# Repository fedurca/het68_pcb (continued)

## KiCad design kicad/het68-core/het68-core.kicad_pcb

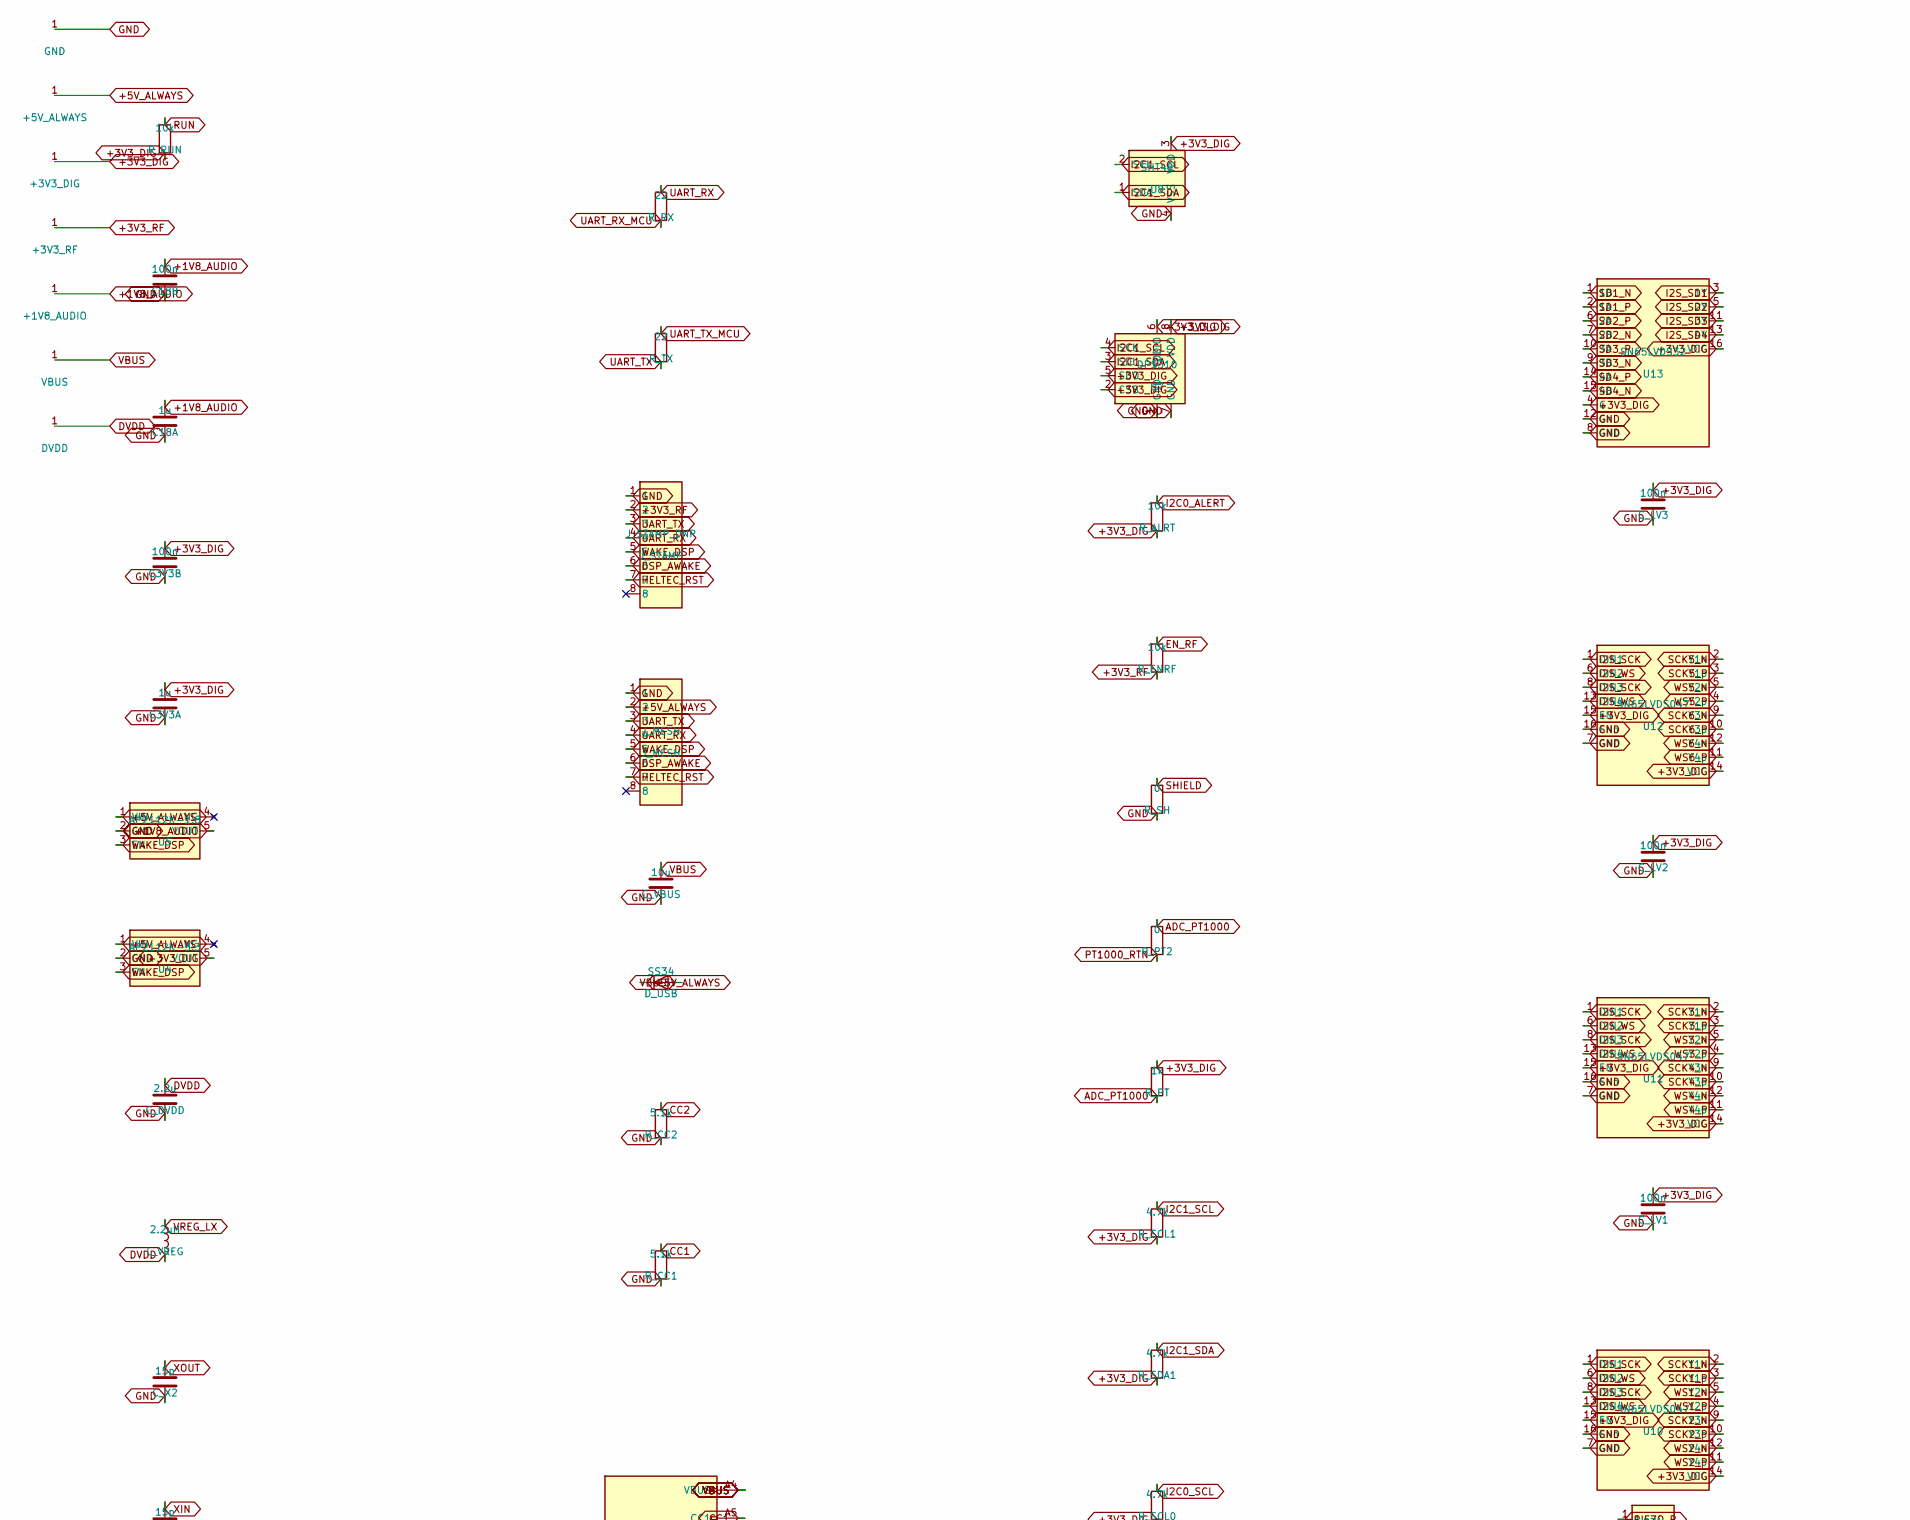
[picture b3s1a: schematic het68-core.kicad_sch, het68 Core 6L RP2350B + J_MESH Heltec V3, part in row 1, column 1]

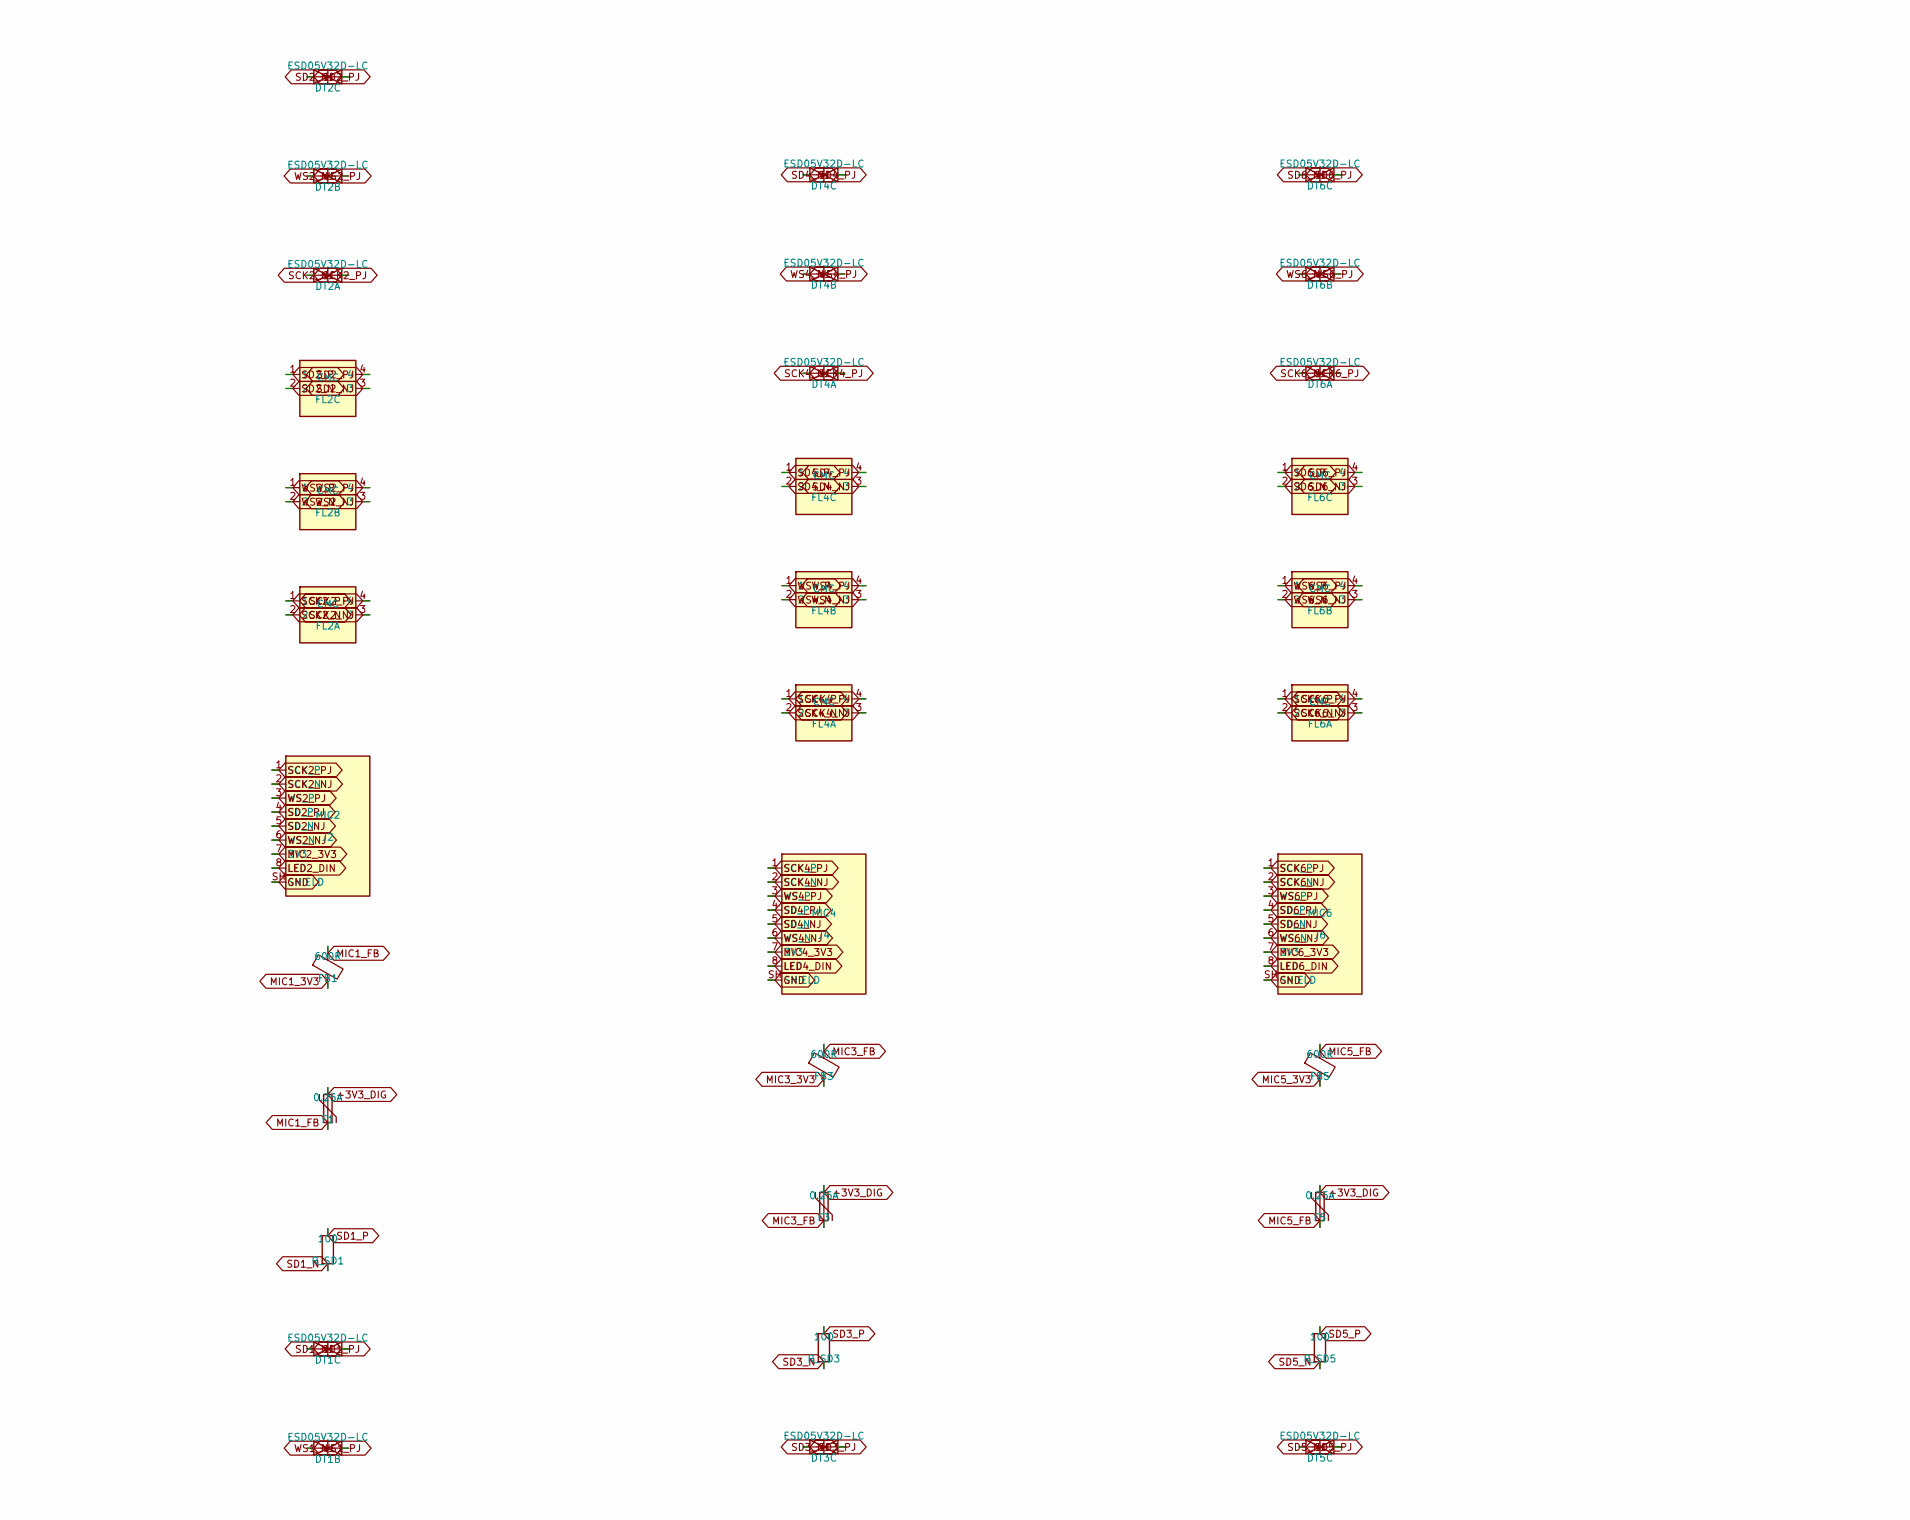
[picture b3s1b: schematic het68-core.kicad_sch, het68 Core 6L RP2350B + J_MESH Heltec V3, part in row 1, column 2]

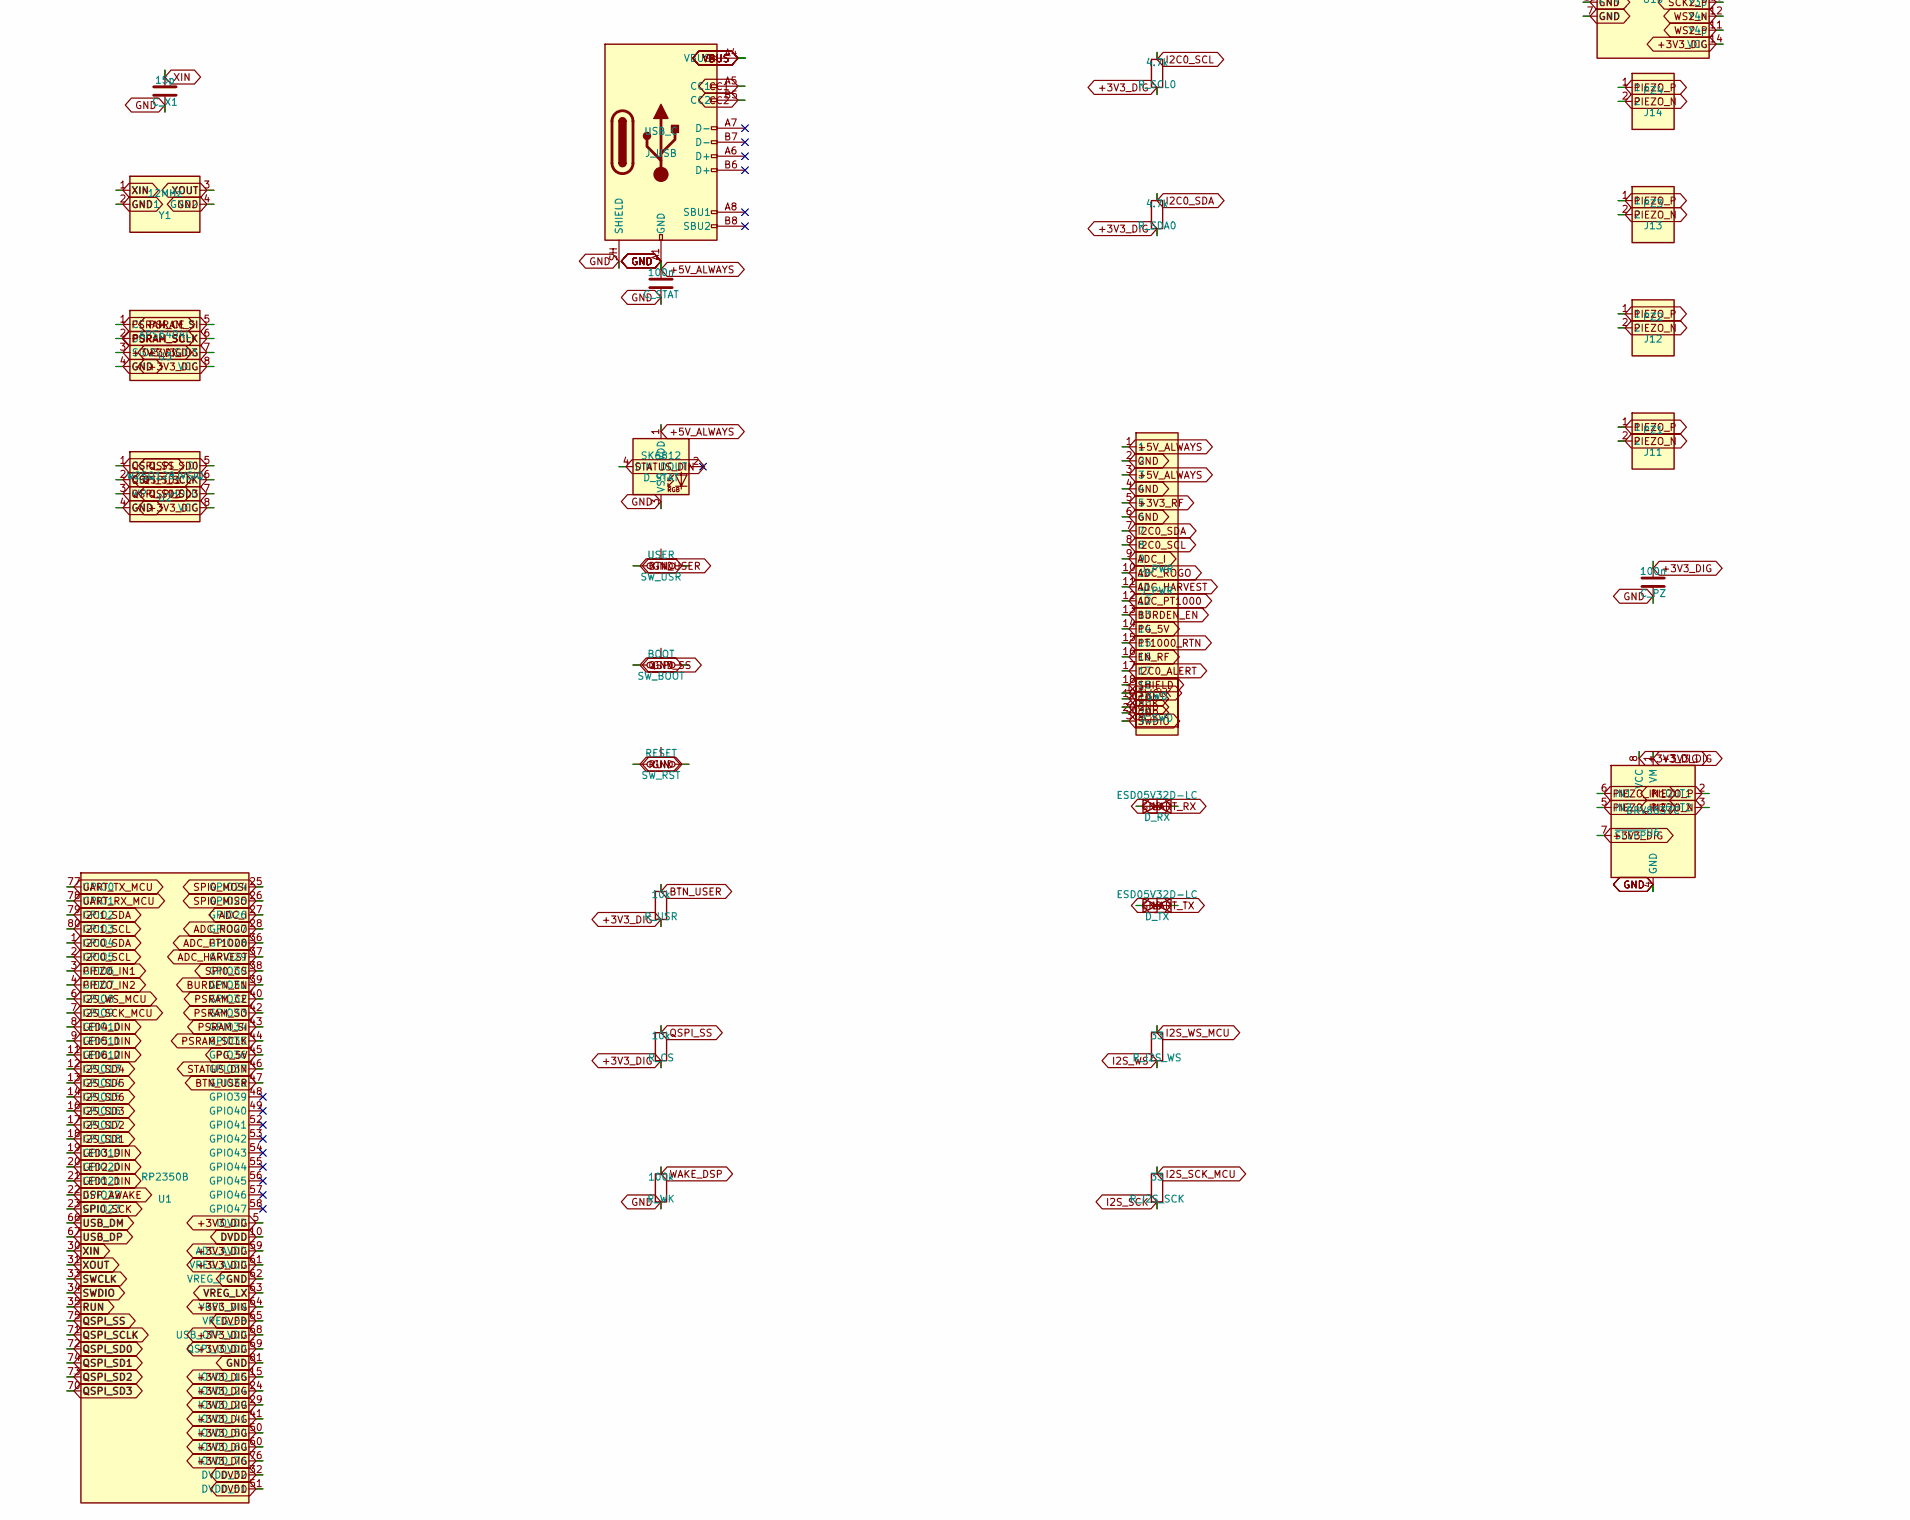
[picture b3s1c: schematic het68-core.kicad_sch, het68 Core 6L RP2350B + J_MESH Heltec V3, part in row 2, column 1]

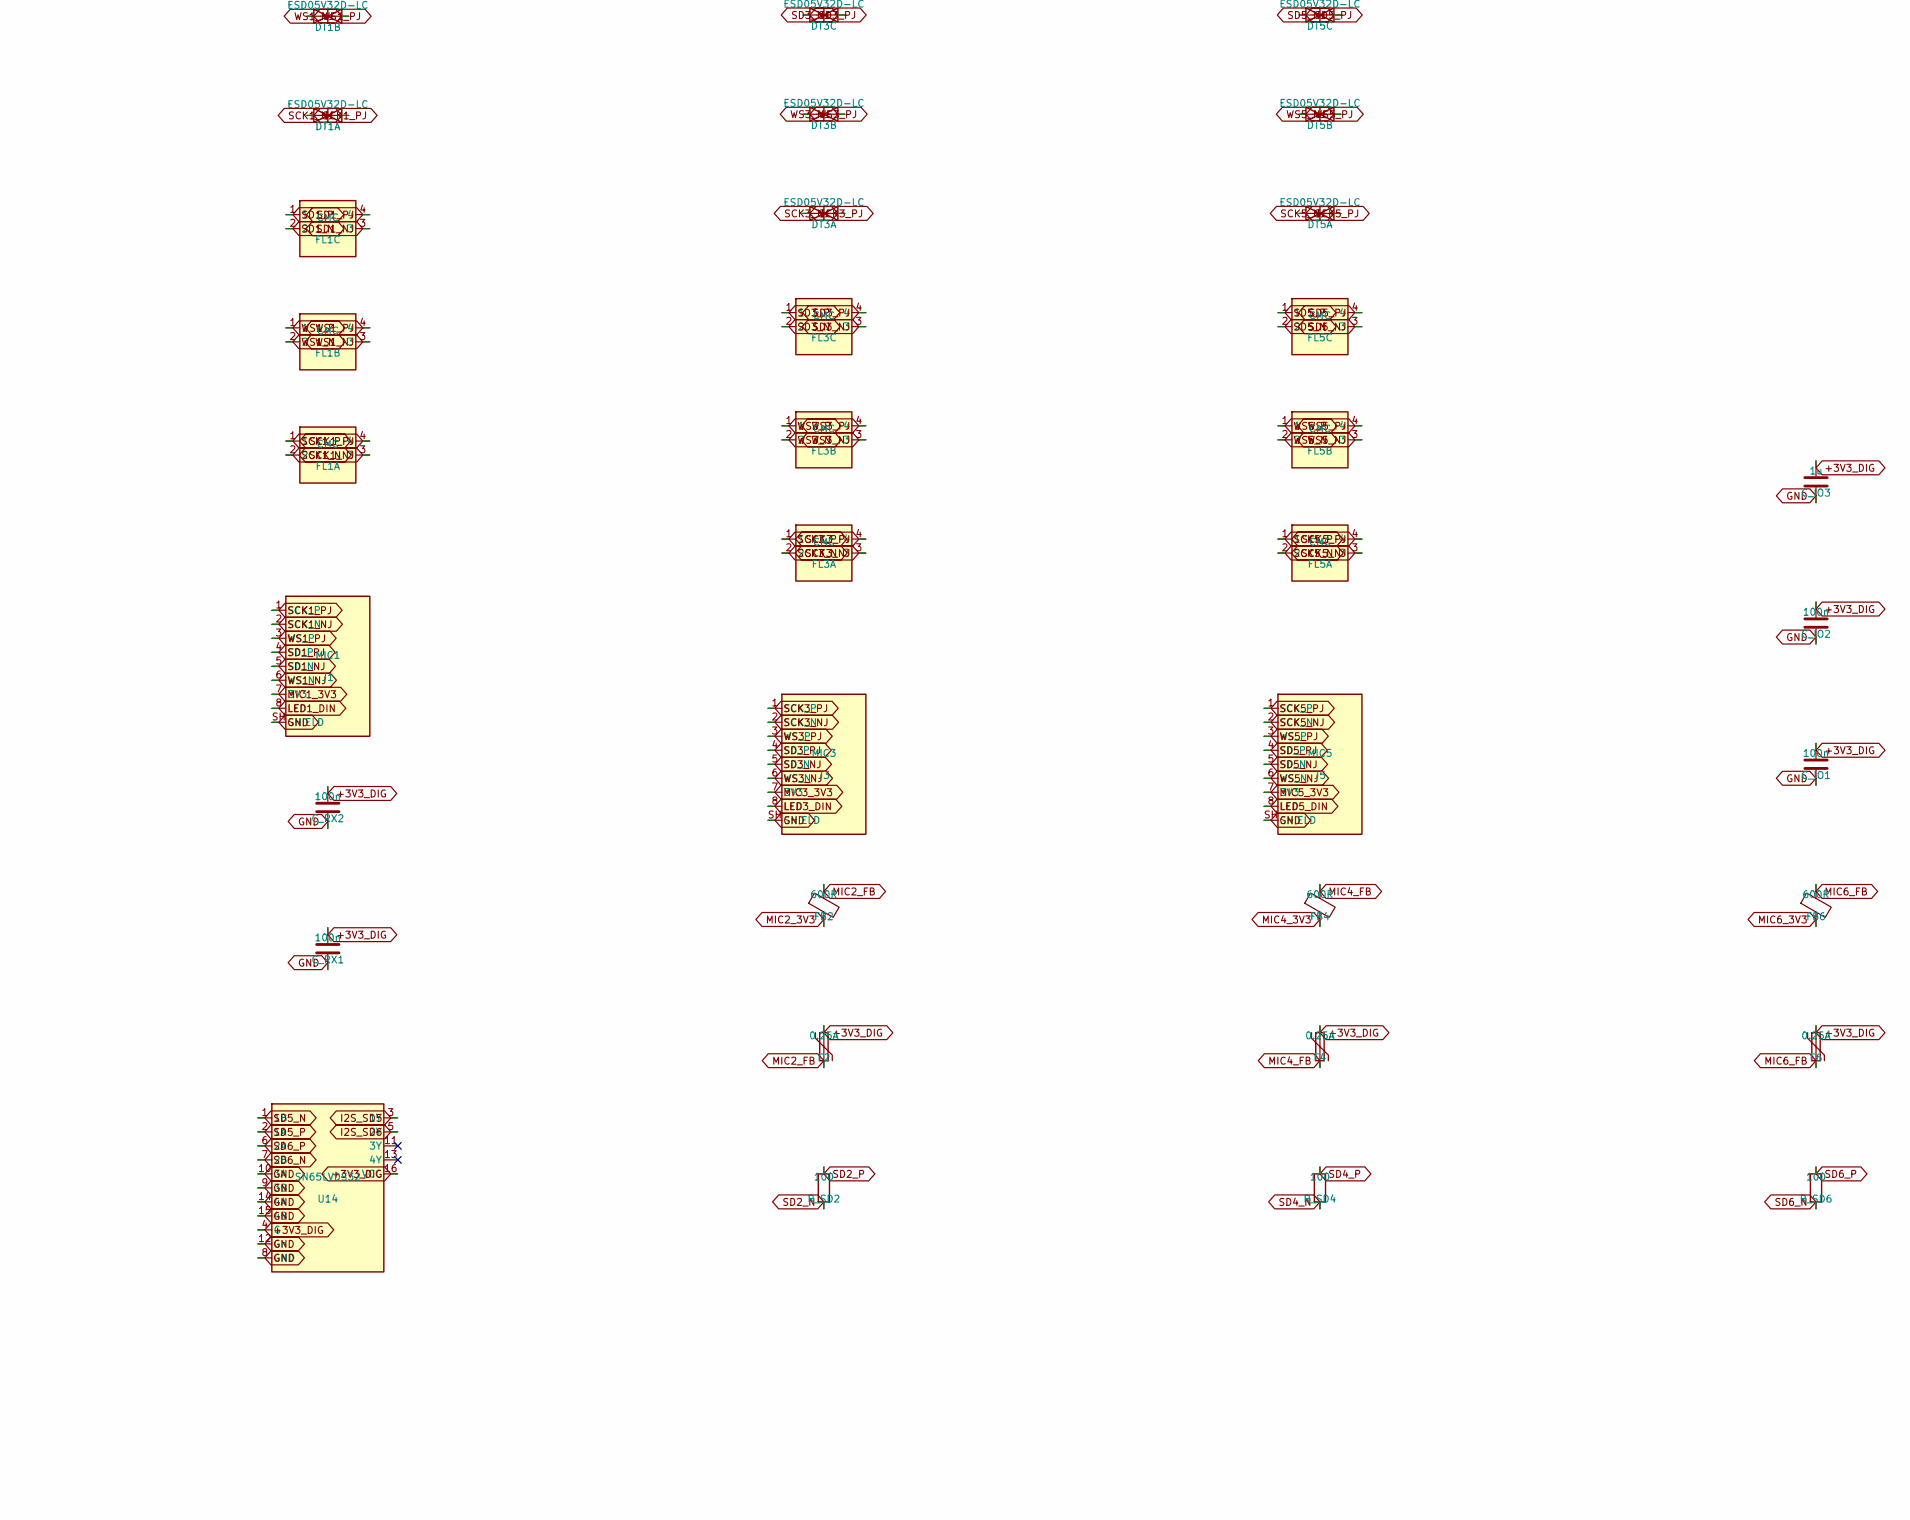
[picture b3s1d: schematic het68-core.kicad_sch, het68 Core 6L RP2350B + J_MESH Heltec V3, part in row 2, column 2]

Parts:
C3V3A, C18A: 1u; C_0603_1608Metric; MPN CL10A105KA8NNNC
C3V3B, C18B: 100n; C_0603_1608Metric; MPN CL10B104KB8NNNC
C_DVDD: 2.2u; C_0805_2012Metric; MPN CL21A225KOFNNNE
C_IO1, C_IO2: 100n; C_0603_1608Metric; MPN CL10B104KB8NNNC
C_IO3: 1u; C_0603_1608Metric; MPN CL10A105KA8NNNC
C_LV1, C_LV2, C_LV3: 100n; C_0603_1608Metric; MPN CL10B104KB8NNNC
C_PZ: 100n; C_0603_1608Metric; MPN CL10B104KB8NNNC
C_RX1, C_RX2: 100n; C_0603_1608Metric; MPN CL10B104KB8NNNC
C_STAT: 100n; C_0603_1608Metric; MPN CL10B104KB8NNNC
C_VBUS: 10u; C_0805_2012Metric; MPN CL21A106KOQNNNE
C_X1, C_X2: 15p; C_0603_1608Metric; MPN CL10C150JB8NNNC
DT1A, DT1B, DT1C, DT2A, DT2B, DT2C, DT3A, DT3B, DT3C, DT4A, DT4B, DT4C, DT5A, DT5B, DT5C, DT6A, DT6B, DT6C: ESD05V32D-LC; D_SOD-323; MPN ESD05V32D-LC
D_RX: ESD05V32D-LC; D_SOD-323; MPN ESD05V32D-LC
D_STAT: SK6812; LED_WS2812B_PLCC4_5.0x5.0mm_P3.2mm; MPN SK6812
D_TX: ESD05V32D-LC; D_SOD-323; MPN ESD05V32D-LC
D_USB: SS34; D_SMC; MPN SS34
F1, F2, F3, F4, F5, F6: 0.25A; Fuse_0603_1608Metric; MPN 0603L025/6V
FB1, FB2, FB3, FB4, FB5, FB6: 600R; L_0603_1608Metric; MPN BLM18AG601SN1D
FL1A, FL1B, FL1C, FL2A, FL2B, FL2C, FL3A, FL3B, FL3C, FL4A, FL4B, FL4C, FL5A, FL5B, FL5C, FL6A, FL6B, FL6C: CMC; L_CommonModeChoke_Coilank_ACM2012; MPN ACM2012-900-2P-T001
J1: MIC1; RJ45_Vertical_het68; MPN RJ45-8P8C-VERT
J2: MIC2; RJ45_Vertical_het68; MPN RJ45-8P8C-VERT
J3: MIC3; RJ45_Vertical_het68; MPN RJ45-8P8C-VERT
J4: MIC4; RJ45_Vertical_het68; MPN RJ45-8P8C-VERT
J5: MIC5; RJ45_Vertical_het68; MPN RJ45-8P8C-VERT
J6: MIC6; RJ45_Vertical_het68; MPN RJ45-8P8C-VERT
J11: PZ1; PinHeader_1x02_P2.54mm_Vertical; MPN PS1240
J12: PZ2; PinHeader_1x02_P2.54mm_Vertical; MPN PS1240
J13: PZ3; PinHeader_1x02_P2.54mm_Vertical; MPN PS1240
J14: PZ4; PinHeader_1x02_P2.54mm_Vertical; MPN PS1240
J_MESH: J_MESH; PinHeader_1x08_P2.54mm_Vertical; MPN PinHeader 1x8 Heltec V3
J_PWR: J_PWR; PinHeader_2x10_P2.54mm_Vertical; MPN interconnect 2x10
J_STAMP: J_STAMP_DNP; PinHeader_1x08_P2.54mm_Vertical; MPN DNP stamp RAK class
J_SWD: SWD; PinHeader_1x03_P2.54mm_Vertical; MPN SWD
J_USB: USB_C; USB_C_Receptacle_HRO_TYPE-C-31-M-12; MPN TYPE-C-31-M-12
L_VREG: 2.2uH; L_0805_2012Metric; MPN DFE201210U-2R2M=P2
R_ALRT: 10k; R_0603_1608Metric; MPN RC0603FR-0710KL
R_CC1, R_CC2: 5.1k; R_0603_1608Metric; MPN RC0603FR-075K1L
R_CS: 10k; R_0603_1608Metric; MPN RC0603FR-0710KL
R_ENRF: 10k; R_0603_1608Metric; MPN RC0603FR-0710KL
R_I2S_SCK, R_I2S_WS: 33; R_0603_1608Metric; MPN RC0603FR-0733RL
R_PT: 1k; R_0603_1608Metric; MPN RC0603FR-071KL
R_PT2: 0; R_0603_1608Metric; MPN RC0603FR-070RL
R_RUN: 10k; R_0603_1608Metric; MPN RC0603FR-0710KL
R_RX: 22; R_0603_1608Metric; MPN RC0603FR-0722RL
R_SCL0, R_SCL1: 4.7k; R_0603_1608Metric; MPN RC0603FR-074K7L
R_SD1, R_SD2, R_SD3, R_SD4, R_SD5, R_SD6: 100; R_0603_1608Metric; MPN RC0603FR-07100RL
R_SDA0, R_SDA1: 4.7k; R_0603_1608Metric; MPN RC0603FR-074K7L
R_SH: 0; R_0603_1608Metric; MPN RC0603FR-070RL
R_TX: 22; R_0603_1608Metric; MPN RC0603FR-0722RL
R_USR: 10k; R_0603_1608Metric; MPN RC0603FR-0710KL
R_WK: 100k; R_0603_1608Metric; MPN RC0603FR-07100KL
SW_BOOT: BOOT; SW_SPST_PTS645Sx43SMTR92; MPN PTS645SM43SMTR92LFS
SW_RST: RESET; SW_SPST_PTS645Sx43SMTR92; MPN PTS645SM43SMTR92LFS
SW_USR: USER; SW_SPST_PTS645Sx43SMTR92; MPN PTS645SM43SMTR92LFS
U1: RP2350B; QFN-80-1EP_10x10mm_P0.4mm_EP3.4x3.4mm_ThermalVias; MPN RP2350B
U2: W25Q128JVSIQ; SOIC-8_3.9x4.9mm_P1.27mm; MPN W25Q128JVSIQ
U3: APS6404L; SOIC-8_3.9x4.9mm_P1.27mm; MPN APS6404L-3SQR-SN
U4: AP2112K-3.3; SOT-23-5; MPN AP2112K-3.3TRG1
U5: AP2112K-1.8; SOT-23-5; MPN AP2112K-1.8TRG1
U6: DRV8837C; Texas_DSG0008A_WSON-8-1EP_2x2mm_P0.5mm_EP0.9x1.6mm; MPN DRV8837CDSGR
U7: DPS310; Bosch_LGA-8_2x2.5mm_P0.65mm_ClockwisePinNumbering; MPN DPS310
U8: SHT40; Sensirion_DFN-4_1.5x1.5mm_P0.8mm_SHT4x_NoCentralPad; MPN SHT40-AD1B-R2
U10, U11, U12: SN65LVDS047; TSSOP-16_4.4x5mm_P0.65mm; MPN SN65LVDS047PW
U13, U14: SN65LVDS32; SOIC-16_3.9x9.9mm_P1.27mm; MPN SN65LVDS32D
Y1: 12MHz; Crystal_SMD_3225-4Pin_3.2x2.5mm; MPN CX3225SB12000H0FLJCC

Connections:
+1V8_AUDIO: C18A.1, C18B.1, U5.5 (VOUT)
+3V3_DIG: C3V3A.1, C3V3B.1, C_IO1.1, C_IO2.1, C_IO3.1, C_LV1.1, C_LV2.1, C_LV3.1, C_PZ.1, C_RX1.1, C_RX2.1, F1.1, F2.1, F3.1, F4.1, F5.1, F6.1, R_ALRT.2, R_CS.2, R_PT.1, R_RUN.2, R_SCL0.2, R_SCL1.2, R_SDA0.2, R_SDA1.2, R_USR.2, U1.5 (IOVDD), U1.15 (IOVDD_15), U1.24 (IOVDD_24), U1.29 (IOVDD_29), U1.41 (IOVDD_41), U1.50 (IOVDD_50), U1.59 (ADC_AVDD), U1.60 (IOVDD_60), U1.61 (VREG_AVDD), U1.64 (VREG_VIN), U1.68 (USB_OTP_VDD), U1.69 (QSPI_IOVDD), U1.76 (IOVDD_76), U2.8 (VCC), U3.3 (SIO2), U3.7 (SIO3), U3.8 (VCC), U4.5 (VOUT), U6.1 (VM), U6.7 (~SLEEP), U6.8 (VCC), U7.2 (CSB), U7.5 (SDO), U7.6 (VDDIO), U7.8 (VDD), U8.3 (VDD), U10.14 (VCC), U10.15 (EN), U11.14 (VCC), U11.15 (EN), U12.14 (VCC), U12.15 (EN), U13.4 (G), U13.16 (VCC), U14.4 (G), U14.16 (VCC)
+3V3_RF: J_PWR.5, J_STAMP.2, R_ENRF.2
+5V_ALWAYS: C_STAT.1, D_STAT.1 (VDD), D_USB.1 (K), J_MESH.2, J_PWR.1, J_PWR.3, U4.1 (VIN), U5.1 (VIN)
ADC_HARVEST: J_PWR.11, U1.37 (GPIO29)
ADC_I: J_PWR.9, U1.27 (GPIO26)
ADC_PT1000: J_PWR.12, R_PT.2, R_PT2.1, U1.36 (GPIO28)
ADC_ROGO: J_PWR.10, U1.28 (GPIO27)
BTN_USER: R_USR.1, SW_USR.1, U1.47 (GPIO38)
BURDEN_EN: J_PWR.13, U1.39 (GPIO31)
CC1: J_USB.A5 (CC1), R_CC1.1
CC2: J_USB.B5 (CC2), R_CC2.1
DSP_AWAKE: J_MESH.6, J_STAMP.6, U1.22 (GPIO22)
DVDD: C_DVDD.1, L_VREG.2, U1.10 (DVDD), U1.32 (DVDD_32), U1.51 (DVDD_51), U1.65 (VREG_FB)
EN_RF: J_PWR.16, R_ENRF.1
GND: C3V3A.2, C3V3B.2, C18A.2, C18B.2, C_DVDD.2, C_IO1.2, C_IO2.2, C_IO3.2, C_LV1.2, C_LV2.2, C_LV3.2, C_PZ.2, C_RX1.2, C_RX2.2, C_STAT.2, C_VBUS.2, C_X1.2, C_X2.2, D_RX.2 (A2), D_STAT.3 (VSS), D_TX.2 (A2), J1.SH (SHIELD), J2.SH (SHIELD), J3.SH (SHIELD), J4.SH (SHIELD), J5.SH (SHIELD), J6.SH (SHIELD), J_MESH.1, J_PWR.2, J_PWR.4, J_PWR.6, J_PWR.19, J_PWR.20, J_STAMP.1, J_SWD.2, J_USB.A1 (GND), J_USB.A12 (GND), J_USB.B1 (GND), J_USB.B12 (GND), J_USB.SH (SHIELD), R_CC1.2, R_CC2.2, R_SH.2, R_WK.2, SW_BOOT.2, SW_RST.2, SW_USR.2, U1.62 (VREG_PGND), U1.81 (GND), U2.4 (GND), U3.4 (GND), U4.2 (GND), U5.2 (GND), U6.4 (GND), U6.9 (GND), U7.1 (GND), U7.7 (GND), U8.4 (VSS), U10.7 (GND), U10.16 (ENn), U11.7 (GND), U11.16 (ENn), U12.7 (GND), U12.16 (ENn), U13.8 (GND), U13.12 (Gn), U14.8 (GND), U14.9 (3B), U14.10 (3A), U14.12 (Gn), U14.14 (4A), U14.15 (4B), Y1.2 (GND1), Y1.4 (GND2)
HELTEC_RST: J_MESH.7, J_STAMP.7
I2C0_ALERT: J_PWR.17, R_ALRT.1
I2C0_SCL: J_PWR.8, R_SCL0.1, U1.2 (GPIO5)
I2C0_SDA: J_PWR.7, R_SDA0.1, U1.1 (GPIO4)
I2C1_SCL: R_SCL1.1, U1.80 (GPIO3), U7.4 (SCK), U8.2 (SCL)
I2C1_SDA: R_SDA1.1, U1.79 (GPIO2), U7.3 (SDI), U8.1 (SDA)
I2S_SCK: R_I2S_SCK.2, U10.1 (DIN1), U10.8 (DIN3), U11.1 (DIN1), U11.8 (DIN3), U12.1 (DIN1), U12.8 (DIN3)
I2S_SCK_MCU: R_I2S_SCK.1, U1.7 (GPIO9)
I2S_SD1: U1.18 (GPIO18), U13.3 (1Y)
I2S_SD2: U1.17 (GPIO17), U13.5 (2Y)
I2S_SD3: U1.16 (GPIO16), U13.11 (3Y)
I2S_SD4: U1.12 (GPIO13), U13.13 (4Y)
I2S_SD5: U1.13 (GPIO14), U14.3 (1Y)
I2S_SD6: U1.14 (GPIO15), U14.5 (2Y)
I2S_WS: R_I2S_WS.2, U10.6 (DIN2), U10.13 (DIN4), U11.6 (DIN2), U11.13 (DIN4), U12.6 (DIN2), U12.13 (DIN4)
I2S_WS_MCU: R_I2S_WS.1, U1.6 (GPIO8)
LED1_DIN: J1.8 (LED), U1.21 (GPIO21)
LED2_DIN: J2.8 (LED), U1.20 (GPIO20)
LED3_DIN: J3.8 (LED), U1.19 (GPIO19)
LED4_DIN: J4.8 (LED), U1.8 (GPIO10)
LED5_DIN: J5.8 (LED), U1.9 (GPIO11)
LED6_DIN: J6.8 (LED), U1.11 (GPIO12)
MIC1_3V3: FB1.2, J1.7 (3V3)
MIC1_FB: F1.2, FB1.1
MIC2_3V3: FB2.2, J2.7 (3V3)
MIC2_FB: F2.2, FB2.1
MIC3_3V3: FB3.2, J3.7 (3V3)
MIC3_FB: F3.2, FB3.1
MIC4_3V3: FB4.2, J4.7 (3V3)
MIC4_FB: F4.2, FB4.1
MIC5_3V3: FB5.2, J5.7 (3V3)
MIC5_FB: F5.2, FB5.1
MIC6_3V3: FB6.2, J6.7 (3V3)
MIC6_FB: F6.2, FB6.1
PG_5V: J_PWR.14, U1.45 (GPIO36)
PIEZO_IN1: U1.3 (GPIO6), U6.6 (IN1)
PIEZO_IN2: U1.4 (GPIO7), U6.5 (IN2)
PIEZO_N: J11.2, J12.2, J13.2, J14.2, U6.3 (OUT2)
PIEZO_P: J11.1, J12.1, J13.1, J14.1, U6.2 (OUT1)
PSRAM_CE: U1.40 (GPIO32), U3.1 (CE)
PSRAM_SCLK: U1.44 (GPIO35), U3.6 (SCLK)
PSRAM_SI: U1.43 (GPIO34), U3.5 (SI)
PSRAM_SO: U1.42 (GPIO33), U3.2 (SO)
PT1000_RTN: J_PWR.15, R_PT2.2
QSPI_SCLK: U1.71 (QSPI_SCLK), U2.6 (CLK)
QSPI_SD0: U1.72 (QSPI_SD0), U2.5 (DI)
QSPI_SD1: U1.74 (QSPI_SD1), U2.2 (DO)
QSPI_SD2: U1.73 (QSPI_SD2), U2.3 (WP)
QSPI_SD3: U1.70 (QSPI_SD3), U2.7 (HOLD)
QSPI_SS: R_CS.1, SW_BOOT.1, U1.75 (QSPI_SS), U2.1 (CS)
RUN: R_RUN.1, SW_RST.1, U1.35 (RUN)
SCK1_N: FL1A.2, U10.2 (Y1n)
SCK1_NJ: DT1A.2 (A2), FL1A.3, J1.2 (SCK_N)
SCK1_P: FL1A.1, U10.3 (Y1p)
SCK1_PJ: DT1A.1 (A1), FL1A.4, J1.1 (SCK_P)
SCK2_N: FL2A.2, U10.9 (Y3n)
SCK2_NJ: DT2A.2 (A2), FL2A.3, J2.2 (SCK_N)
SCK2_P: FL2A.1, U10.10 (Y3p)
SCK2_PJ: DT2A.1 (A1), FL2A.4, J2.1 (SCK_P)
SCK3_N: FL3A.2, U11.2 (Y1n)
SCK3_NJ: DT3A.2 (A2), FL3A.3, J3.2 (SCK_N)
SCK3_P: FL3A.1, U11.3 (Y1p)
SCK3_PJ: DT3A.1 (A1), FL3A.4, J3.1 (SCK_P)
SCK4_N: FL4A.2, U11.9 (Y3n)
SCK4_NJ: DT4A.2 (A2), FL4A.3, J4.2 (SCK_N)
SCK4_P: FL4A.1, U11.10 (Y3p)
SCK4_PJ: DT4A.1 (A1), FL4A.4, J4.1 (SCK_P)
SCK5_N: FL5A.2, U12.2 (Y1n)
SCK5_NJ: DT5A.2 (A2), FL5A.3, J5.2 (SCK_N)
SCK5_P: FL5A.1, U12.3 (Y1p)
SCK5_PJ: DT5A.1 (A1), FL5A.4, J5.1 (SCK_P)
SCK6_N: FL6A.2, U12.9 (Y3n)
SCK6_NJ: DT6A.2 (A2), FL6A.3, J6.2 (SCK_N)
SCK6_P: FL6A.1, U12.10 (Y3p)
SCK6_PJ: DT6A.1 (A1), FL6A.4, J6.1 (SCK_P)
SD1_N: FL1C.2, R_SD1.2, U13.1 (1B)
SD1_NJ: DT1C.2 (A2), FL1C.3, J1.5 (SD_N)
SD1_P: FL1C.1, R_SD1.1, U13.2 (1A)
SD1_PJ: DT1C.1 (A1), FL1C.4, J1.4 (SD_P)
SD2_N: FL2C.2, R_SD2.2, U13.7 (2B)
SD2_NJ: DT2C.2 (A2), FL2C.3, J2.5 (SD_N)
SD2_P: FL2C.1, R_SD2.1, U13.6 (2A)
SD2_PJ: DT2C.1 (A1), FL2C.4, J2.4 (SD_P)
SD3_N: FL3C.2, R_SD3.2, U13.9 (3B)
SD3_NJ: DT3C.2 (A2), FL3C.3, J3.5 (SD_N)
SD3_P: FL3C.1, R_SD3.1, U13.10 (3A)
SD3_PJ: DT3C.1 (A1), FL3C.4, J3.4 (SD_P)
SD4_N: FL4C.2, R_SD4.2, U13.15 (4B)
SD4_NJ: DT4C.2 (A2), FL4C.3, J4.5 (SD_N)
SD4_P: FL4C.1, R_SD4.1, U13.14 (4A)
SD4_PJ: DT4C.1 (A1), FL4C.4, J4.4 (SD_P)
SD5_N: FL5C.2, R_SD5.2, U14.1 (1B)
SD5_NJ: DT5C.2 (A2), FL5C.3, J5.5 (SD_N)
SD5_P: FL5C.1, R_SD5.1, U14.2 (1A)
SD5_PJ: DT5C.1 (A1), FL5C.4, J5.4 (SD_P)
SD6_N: FL6C.2, R_SD6.2, U14.7 (2B)
SD6_NJ: DT6C.2 (A2), FL6C.3, J6.5 (SD_N)
SD6_P: FL6C.1, R_SD6.1, U14.6 (2A)
SD6_PJ: DT6C.1 (A1), FL6C.4, J6.4 (SD_P)
SHIELD: J_PWR.18, R_SH.1
SPI0_CS: U1.38 (GPIO30)
SPI0_MISO: U1.26 (GPIO25)
SPI0_MOSI: U1.25 (GPIO24)
SPI0_SCK: U1.23 (GPIO23)
STATUS_DIN: D_STAT.4 (DIN), U1.46 (GPIO37)
SWCLK: J_SWD.1, U1.33 (SWCLK)
SWDIO: J_SWD.3, U1.34 (SWDIO)
UART_RX: D_RX.1 (A1), J_MESH.4, J_STAMP.4, R_RX.1
UART_RX_MCU: R_RX.2, U1.78 (GPIO1)
UART_TX: D_TX.1 (A1), J_MESH.3, J_STAMP.3, R_TX.2
UART_TX_MCU: R_TX.1, U1.77 (GPIO0)
USB_DM: U1.66 (USB_DM)
USB_DP: U1.67 (USB_DP)
VBUS: C_VBUS.1, D_USB.2 (A), J_USB.A4 (VBUS), J_USB.A9 (VBUS), J_USB.B4 (VBUS), J_USB.B9 (VBUS)
VREG_LX: L_VREG.1, U1.63 (VREG_LX)
WAKE_DSP: J_MESH.5, J_STAMP.5, R_WK.1, U4.3 (EN), U5.3 (EN)
WS1_N: FL1B.2, U10.5 (Y2n)
WS1_NJ: DT1B.2 (A2), FL1B.3, J1.6 (WS_N)
WS1_P: FL1B.1, U10.4 (Y2p)
WS1_PJ: DT1B.1 (A1), FL1B.4, J1.3 (WS_P)
WS2_N: FL2B.2, U10.12 (Y4n)
WS2_NJ: DT2B.2 (A2), FL2B.3, J2.6 (WS_N)
WS2_P: FL2B.1, U10.11 (Y4p)
WS2_PJ: DT2B.1 (A1), FL2B.4, J2.3 (WS_P)
WS3_N: FL3B.2, U11.5 (Y2n)
WS3_NJ: DT3B.2 (A2), FL3B.3, J3.6 (WS_N)
WS3_P: FL3B.1, U11.4 (Y2p)
WS3_PJ: DT3B.1 (A1), FL3B.4, J3.3 (WS_P)
WS4_N: FL4B.2, U11.12 (Y4n)
WS4_NJ: DT4B.2 (A2), FL4B.3, J4.6 (WS_N)
WS4_P: FL4B.1, U11.11 (Y4p)
WS4_PJ: DT4B.1 (A1), FL4B.4, J4.3 (WS_P)
WS5_N: FL5B.2, U12.5 (Y2n)
WS5_NJ: DT5B.2 (A2), FL5B.3, J5.6 (WS_N)
WS5_P: FL5B.1, U12.4 (Y2p)
WS5_PJ: DT5B.1 (A1), FL5B.4, J5.3 (WS_P)
WS6_N: FL6B.2, U12.12 (Y4n)
WS6_NJ: DT6B.2 (A2), FL6B.3, J6.6 (WS_N)
WS6_P: FL6B.1, U12.11 (Y4p)
WS6_PJ: DT6B.1 (A1), FL6B.4, J6.3 (WS_P)
XIN: C_X1.1, U1.30 (XIN), Y1.1 (XIN)
XOUT: C_X2.1, U1.31 (XOUT), Y1.3 (XOUT)

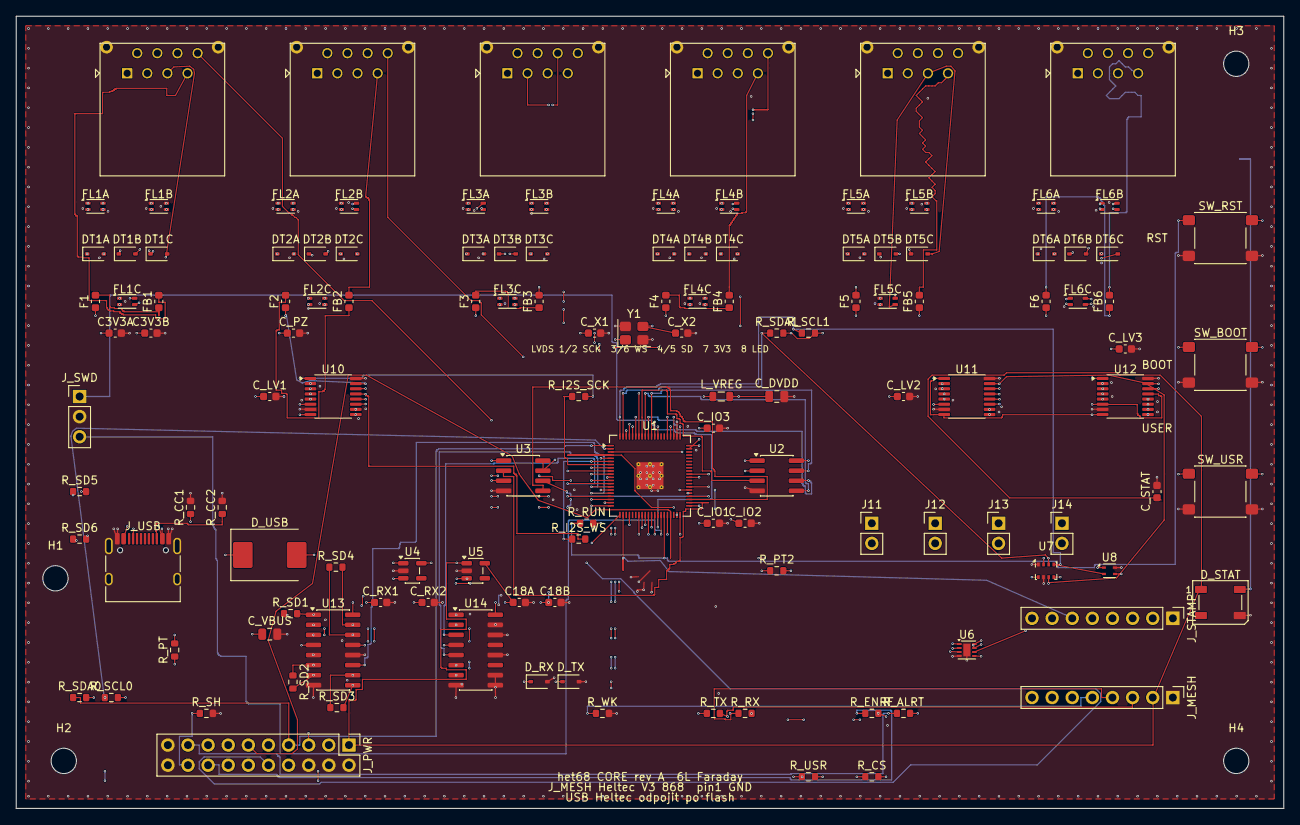
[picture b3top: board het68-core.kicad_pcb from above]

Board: 8 copper layers, 160.0 x 100.0 mm, 132 parts (0 on the bottom side), 152 nets.

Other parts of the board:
H1, H2, H3, H4: M3; MountingHole_3.2mm_M3
